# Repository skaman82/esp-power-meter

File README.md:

# **ESP PowerMeter**

Energy logging und current/voltage meter. Solar panel tester and a Home Assistant MQTT battery sensor
---
Web Interface:

## **Features**
- **3 Modes:** Coulometer / Solar Tester / Power Meter  
- **3 Battery Types Supported:** Li-ion, LiPo, LiFePO4  
- Fully configurable with **OLED UI**  
- **Wi-Fi Support:** Access Point mode or join an existing network  
- Additional **Web Interface**  
- **MQTT Support:** can be used as a sensor with Home Assistant  
- **Max Voltage:** 36V (listed 5V BEC supports max. 30V)  

---

## **Parts needed**
- **ESP32-C3 PRO MINI**  
- **5V BEC** (iFlight 5V 2-8S)  
- **INA226 Module** + 3920 5W 2mΩ Shunt (R002)  
 *or* custom INA226 PCB (see Hardware directory)
- **male/female XT60 connectors*
- **1.5" 128x128 I2C OLED Display** *(optional)*  
- **2x Tactile Buttons** *(optional)*
- **Real Time Clock RTC DS3231 module** *(optional)*  
- **3D Printed Case** (see STLs directory)  

## **RTC and NON-RTC Versions**
The main difference to the non-RTC version ist that the RTC version of the code uses an DS3231 real time clock for measurement and displays graph labels with the correct time in the Web-UI. 

---

Device Image:

## **Button Mapping**

## **MQTT Entities in Home Assistant**

Custom INA266 Sensor PCB with optional DS3231:

## **Connection Diagram**
*To be determined (TBD)*  

---

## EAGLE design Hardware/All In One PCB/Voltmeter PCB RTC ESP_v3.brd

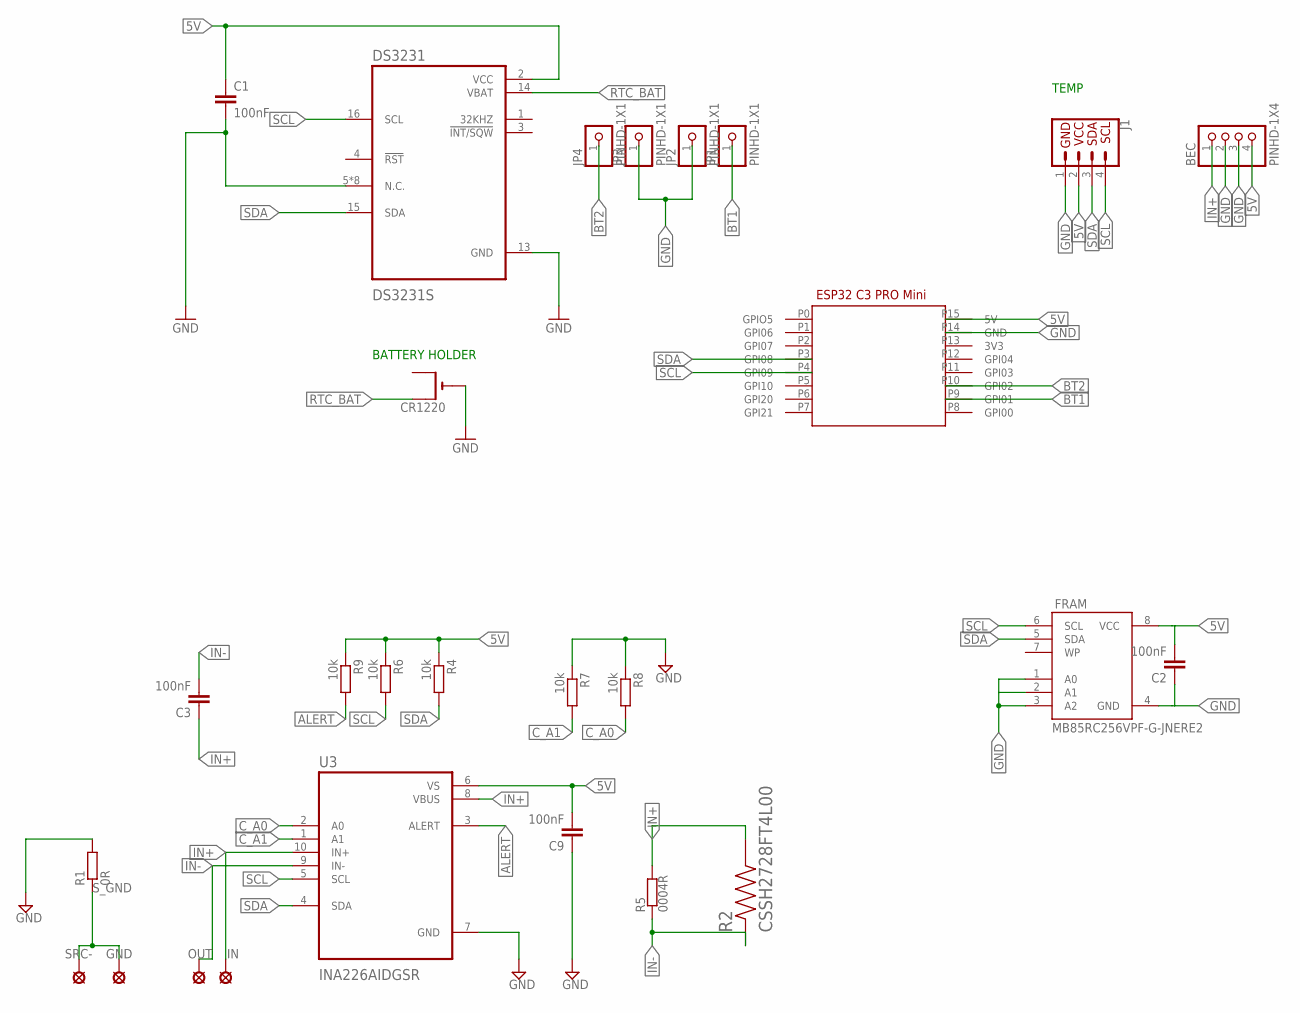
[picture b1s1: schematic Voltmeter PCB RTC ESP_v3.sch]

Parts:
BEC: PINHD-1X4; 1X04
C1, C2, C3, C9: 100nF; C0603
CR1220: CR1220SMT; CR1220-SMD
DS3231: DS3231S; SOIC127P1032X265-16N
FRAM: MB85RC256VPF-G-JNERE2; SOIC8_208MIL
GND: SE14
IN: SE14
J1: QWIIC_CONNECTORJS-1MM; 1X04_1MM_RA
JP1, JP2, JP3, JP4: PINHD-1X1; 1X01
OUT: SE14
R1: 0R; R1206
R2: CSSH2728FT4L00; RESC6771X124N
R4, R6, R7, R8, R9: 10k; R0603
R5: 0004R; BVS
SRC-: SE14
U3: INA226AIDGSR; SOP50P490X110-10N
U$1: ESP32_C3_PROV1; ESP32_C2_PRO

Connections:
5V: BEC.4, C1.1, C2.2, C9.2, DS3231.2 (VCC), FRAM.8 (VCC), J1.2 (VCC), R4.1, R6.1, R9.1, U3.6 (VS), U$1.P15 (5V)
ALERT: R9.2, U3.3 (ALERT)
BT1: JP1.1, U$1.P9 (GPI01)
BT2: JP4.1, U$1.P10 (GPI02)
C_A0: R8.2, U3.2 (A0)
C_A1: R7.2, U3.1 (A1)
GND: BEC.2, BEC.3, C1.2, C2.1, C9.1, CR1220.-, DS3231.5 (N.C.), DS3231.6 (N.C.), DS3231.7 (N.C.), DS3231.8 (N.C.), DS3231.9 (N.C.), DS3231.10 (N.C.), DS3231.11 (N.C.), DS3231.12 (N.C.), DS3231.13 (GND), FRAM.1 (A0), FRAM.3 (A2), FRAM.4 (GND), J1.1 (GND), JP2.1, JP3.1, R1.2, R7.1, R8.1, U3.7 (GND), U$1.P14 (GND)
IN+: BEC.1, C3.1, IN.MP, R2.2, R5.1, U3.8 (VBUS), U3.10 (IN+)
IN-: C3.2, OUT.MP, R2.1, R5.2, U3.9 (IN-)
RTC_BAT: CR1220.+$1 (+), DS3231.14 (VBAT)
SCL: DS3231.16 (SCL), FRAM.6 (SCL), J1.4 (SCL), R6.2, U3.5 (SCL), U$1.P4 (GPI09)
SDA: DS3231.15 (SDA), FRAM.5 (SDA), J1.3 (SDA), R4.2, U3.4 (SDA), U$1.P3 (GPI08)
S_GND: GND.MP, R1.1, SRC-.MP

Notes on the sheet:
BATTERY HOLDER
TEMP

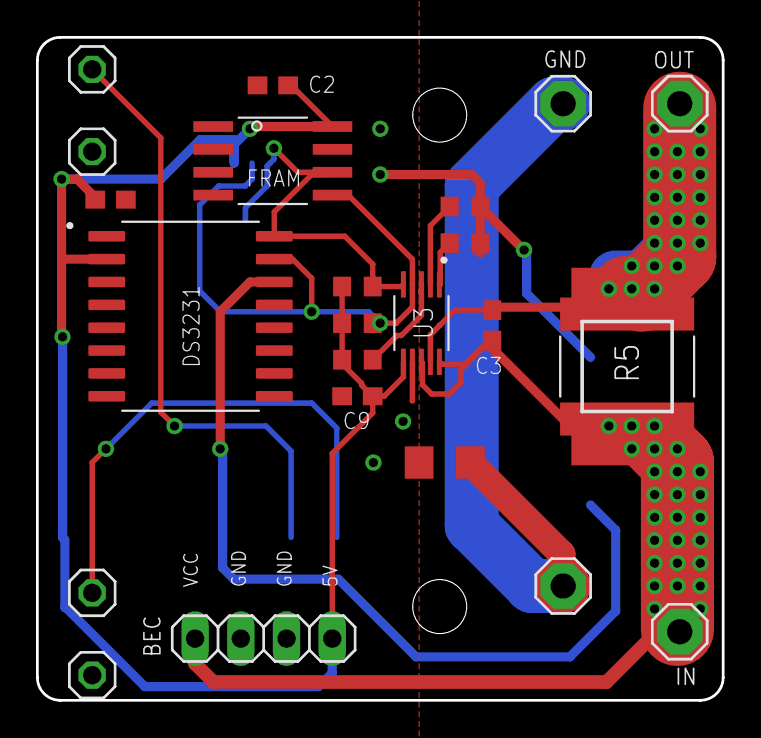
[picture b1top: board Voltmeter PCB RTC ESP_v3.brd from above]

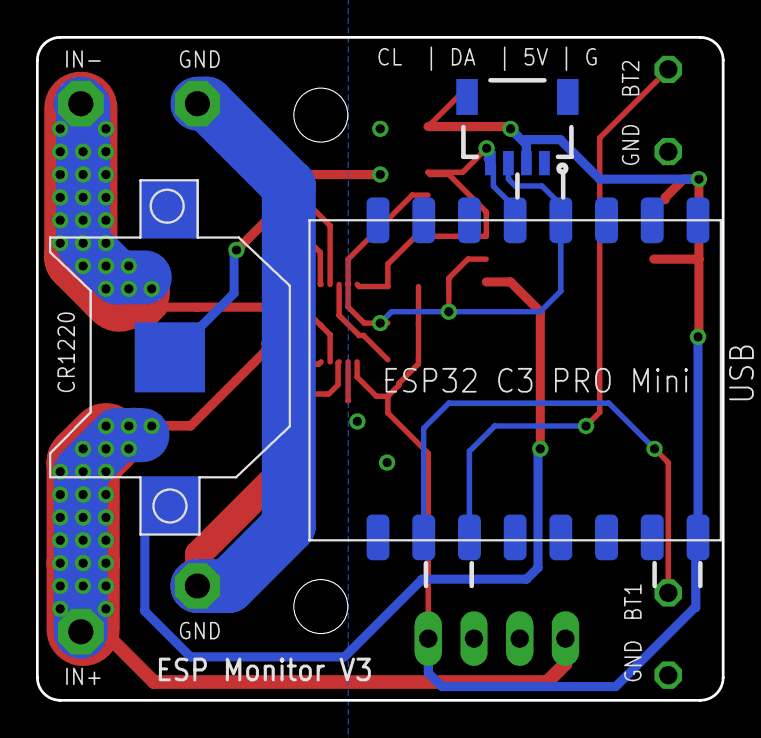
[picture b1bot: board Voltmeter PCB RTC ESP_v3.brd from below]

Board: 2 copper layers, 38.1 x 36.8 mm, 27 parts (3 on the bottom side), 13 nets.

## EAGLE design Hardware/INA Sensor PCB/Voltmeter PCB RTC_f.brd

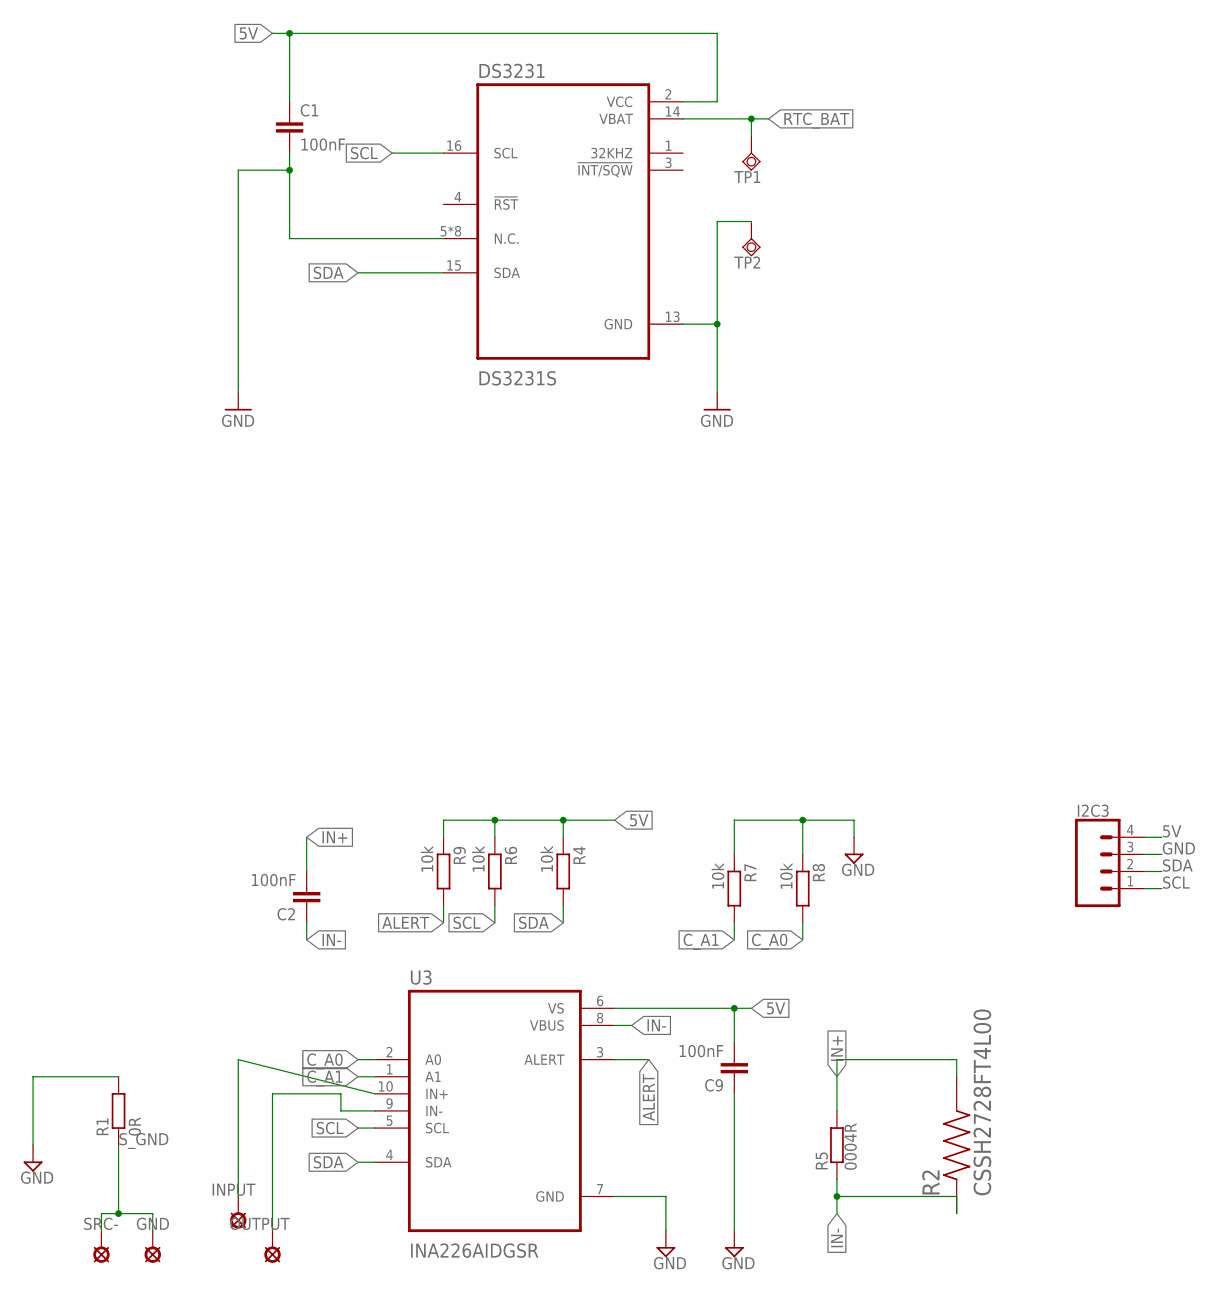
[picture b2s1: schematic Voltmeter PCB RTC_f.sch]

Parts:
C1, C2, C9: 100nF; C0603
DS3231: DS3231S; SOIC127P1032X265-16N
GND: SE14
I2C3: CONN_041X04_NO_SILK; 1X04_NO_SILK
INPUT: SE14
OUTPUT: SE14
R1: 0R; R1206
R2: CSSH2728FT4L00; RESC6771X124N
R4, R6, R7, R8, R9: 10k; R0603
R5: 0004R; BVS
SRC-: SE14
TP1, TP2: TPSQB1,27; B1,27
U3: INA226AIDGSR; SOP50P490X110-10N

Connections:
5V: C1.1, C9.2, DS3231.2 (VCC), I2C3.4, R4.1, R6.1, R9.1, U3.6 (VS)
ALERT: R9.2, U3.3 (ALERT)
C_A0: R8.2, U3.2 (A0)
C_A1: R7.2, U3.1 (A1)
GND: C1.2, C9.1, DS3231.5 (N.C.), DS3231.6 (N.C.), DS3231.7 (N.C.), DS3231.8 (N.C.), DS3231.9 (N.C.), DS3231.10 (N.C.), DS3231.11 (N.C.), DS3231.12 (N.C.), DS3231.13 (GND), I2C3.3, R1.2, R7.1, R8.1, TP2.TP, U3.7 (GND)
IN+: C2.2, OUTPUT.MP, R2.2, R5.1, U3.9 (IN-)
IN-: C2.1, INPUT.MP, R2.1, R5.2, U3.8 (VBUS), U3.10 (IN+)
RTC_BAT: DS3231.14 (VBAT), TP1.TP
SCL: DS3231.16 (SCL), I2C3.1, R6.2, U3.5 (SCL)
SDA: DS3231.15 (SDA), I2C3.2, R4.2, U3.4 (SDA)
S_GND: GND.MP, R1.1, SRC-.MP

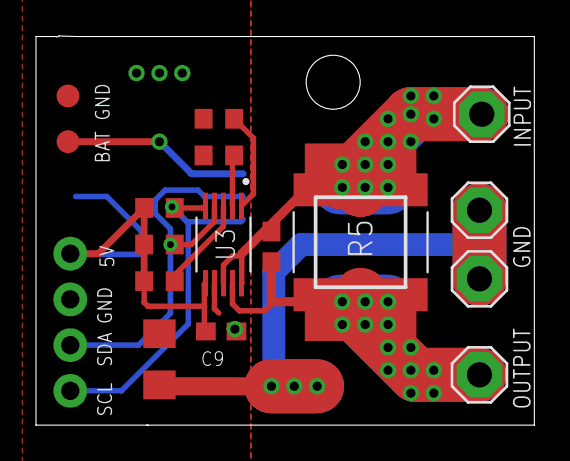
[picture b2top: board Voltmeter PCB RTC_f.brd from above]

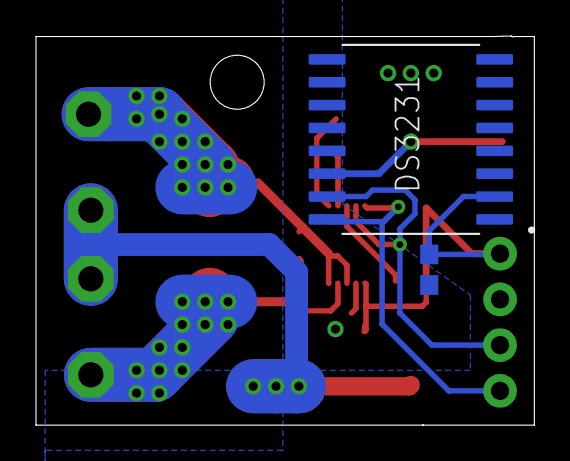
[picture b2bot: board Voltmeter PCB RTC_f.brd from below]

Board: 2 copper layers, 27.7 x 21.6 mm, 20 parts (2 on the bottom side), 11 nets.

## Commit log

2025-07-21 initial upload
2025-07-21 PCBs
2025-07-22 RTC Version
2025-07-22 rtc2
2025-07-22 cleanup
2025-07-23 New hourly logging style
2025-07-23 PCB Update
2025-07-27 stls
2025-07-30 updates
    - MQTT functionality
    - favicon fix
    - OLED display + buttons are now optional
2025-07-31 test
2025-08-04 rework
2025-08-04 new stl
2025-08-04 bugfix
2025-08-04 save bugfix
2025-08-04 mqtt icon change

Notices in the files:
parts and their libraries:
SparkFun-Connectors: Licensing: Creative Commons ShareAlike 4.0 International - https://creativecommons.org/licenses/by-sa/4.0
